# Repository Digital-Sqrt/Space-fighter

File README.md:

***
<p xmlns:cc="http://creativecommons.org/ns#" xmlns:dct="http://purl.org/dc/terms/"><a property="dct:title" rel="cc:attributionURL" href="https://github.com/Digital-Sqrt/Space-fighter">Space-fighter</a> by <a rel="cc:attributionURL dct:creator" property="cc:attributionName" href="https://github.com/Digital-Sqrt">Adrian West</a> is licensed under <a href="http://creativecommons.org/licenses/by-nc-sa/4.0/?ref=chooser-v1" target="_blank" rel="license noopener noreferrer" style="display:inline-block;">Attribution-NonCommercial-ShareAlike 4.0 International<br></a></p>

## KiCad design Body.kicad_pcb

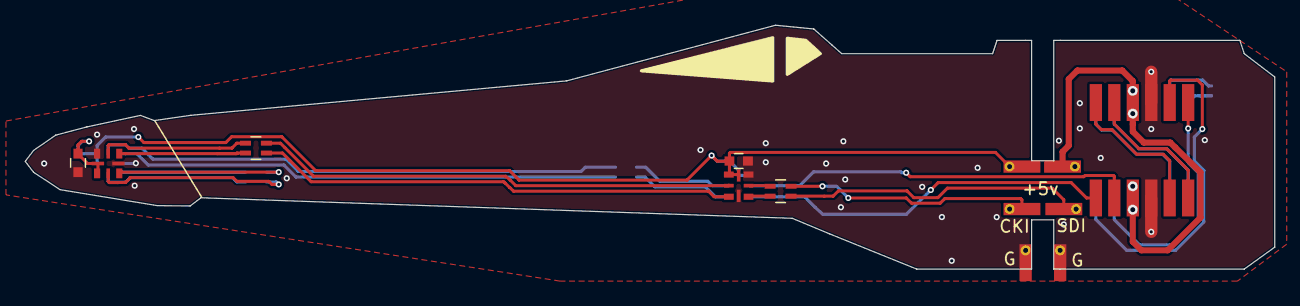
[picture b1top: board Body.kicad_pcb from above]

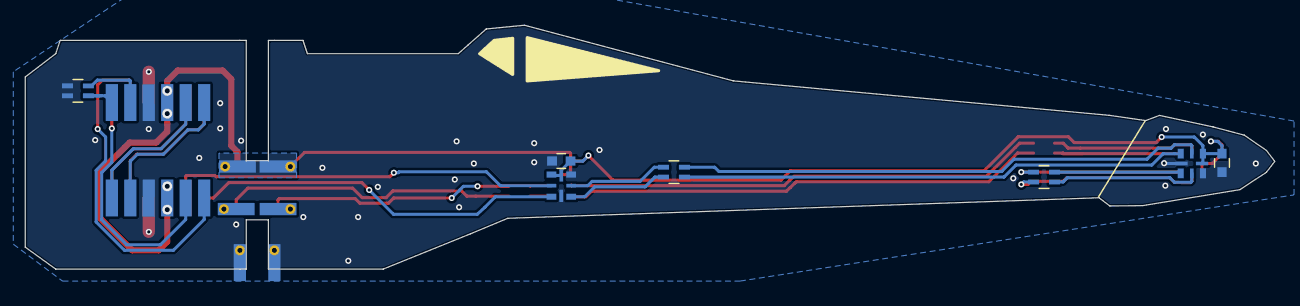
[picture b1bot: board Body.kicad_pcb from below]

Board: 2 copper layers, 101.5 x 19.8 mm, 23 parts (7 on the bottom side), 28 nets.

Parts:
C1, C2, C3, C4: .1uF; C_0603
D1, D2, D3, D4: APA102-2020; APA102-2020_style_2
J7, J8: 6pin_conn; 6pin_top
J9, J10: 6pin_conn; 6pin_bottom
J11, J11#2, J12, J12#2, J13, J14: 1pin_conn; Conn_1_Pin
R1, R2, R3, R4, R5: 33 ohm; R_Array_Concave_2x0603

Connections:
+5V: C1.1, C2.1, C3.1, C4.1, D1.1, D1.7, D2.1, D2.7, D3.1, D3.7, D4.1, D4.7, J7.3, J8.3, J9.3, J10.3, J12.1, J12#2.1
GND: C1.2, C2.2, C3.2, C4.2, D1.6, D1.8, D2.6, D2.8, D3.6, D3.8, D4.6, D4.8, J7.4, J8.4, J9.4, J10.4, J11.1, J11#2.1, R5.3, R5.4
unnamed: D1.2, R2.2
unnamed: D1.3, R2.1
unnamed: D1.4, R1.4
unnamed: D1.5, R1.3
unnamed: D2.2, R3.2
unnamed: D2.3, R3.1
unnamed: D2.4, R2.4
unnamed: D2.5, R2.3
unnamed: D3.2, R4.2
unnamed: D3.3, R4.1
unnamed: D3.4, R3.4
unnamed: D3.5, R3.3
unnamed: D4.2, J7.2
unnamed: D4.3, J7.1
unnamed: D4.4, R4.4
unnamed: D4.5, R4.3
unnamed: J7.5, J8.1
unnamed: J7.6, J8.2
unnamed: J8.5, J9.1
unnamed: J8.6, J9.2
unnamed: J9.5, J10.1
unnamed: J9.6, J10.2
unnamed: J10.5, R5.2
unnamed: J10.6, R5.1
unnamed: J13.1, R1.2
unnamed: J14.1, R1.1

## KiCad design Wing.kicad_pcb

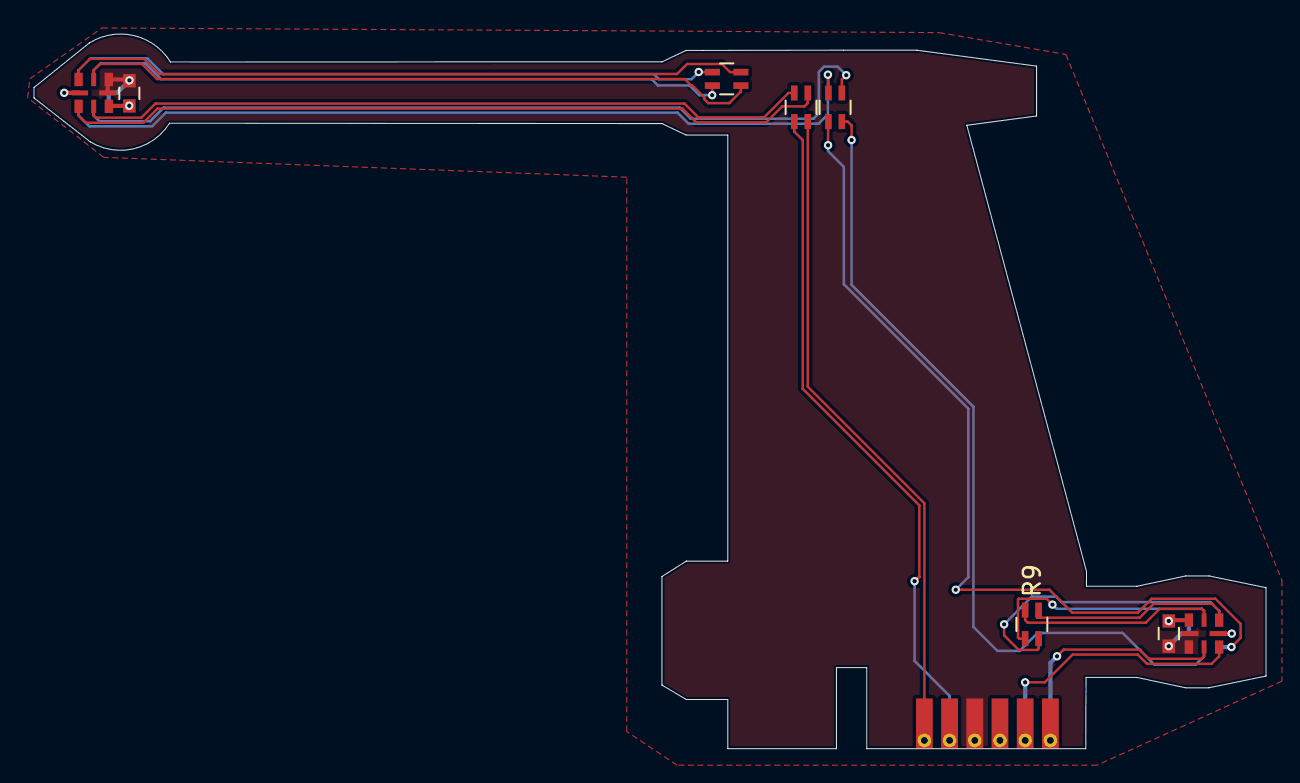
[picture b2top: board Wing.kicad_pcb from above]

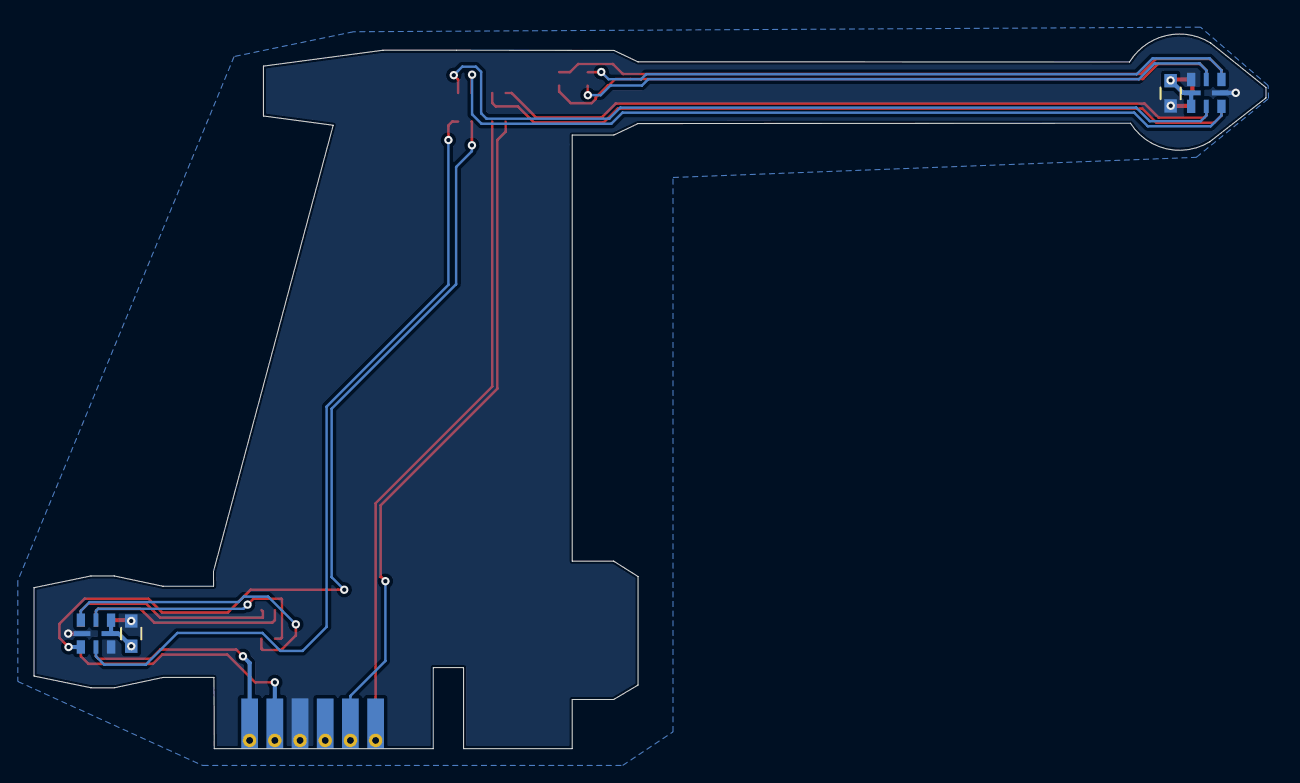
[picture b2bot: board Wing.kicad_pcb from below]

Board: 2 copper layers, 73.3 x 42.5 mm, 13 parts (4 on the bottom side), 20 nets.

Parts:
C5, C6, C7, C8: .1uF; C_0603
D5, D6, D7, D8: APA102-2020; APA102-2020_style_2
J2: 6pin_conn; Connector
R6, R7, R8, R9: 33 ohm; R_Array_Concave_2x0603

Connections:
+5V: C5.1, C6.1, C7.1, C8.1, D5.1, D5.7, D6.1, D6.7, D7.1, D7.7, D8.1, D8.7, J2.3
GND: C5.2, C6.2, C7.2, C8.2, D5.6, D5.8, D6.6, D6.8, D7.6, D7.8, D8.6, D8.8, J2.4
unnamed: D5.2, R7.1
unnamed: D5.3, R7.2
unnamed: D5.4, R6.3
unnamed: D5.5, R6.4
unnamed: D6.2, R8.1
unnamed: D6.3, R8.2
unnamed: D6.4, R7.3
unnamed: D6.5, R7.4
unnamed: D7.2, R9.1
unnamed: D7.3, R9.2
unnamed: D7.4, R8.3
unnamed: D7.5, R8.4
unnamed: D8.2, J2.6
unnamed: D8.3, J2.5
unnamed: D8.4, R9.3
unnamed: D8.5, R9.4
unnamed: J2.1, R6.2
unnamed: J2.2, R6.1

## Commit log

2021-01-16 Create LICENSE
2021-01-23 BOARD CORRECTIONS BASED ON PROTO TYPE
2021-01-24 more media for the instructable
2021-01-27 more pictures for the doc's
2021-02-19 code updates
2021-03-01 Footprint was Jacked for LED - it's been fixed
    foot print for led was incorrect. It aslo seems that some pad resistors are needed
2021-03-23 Board Fixes fort bad footprint
